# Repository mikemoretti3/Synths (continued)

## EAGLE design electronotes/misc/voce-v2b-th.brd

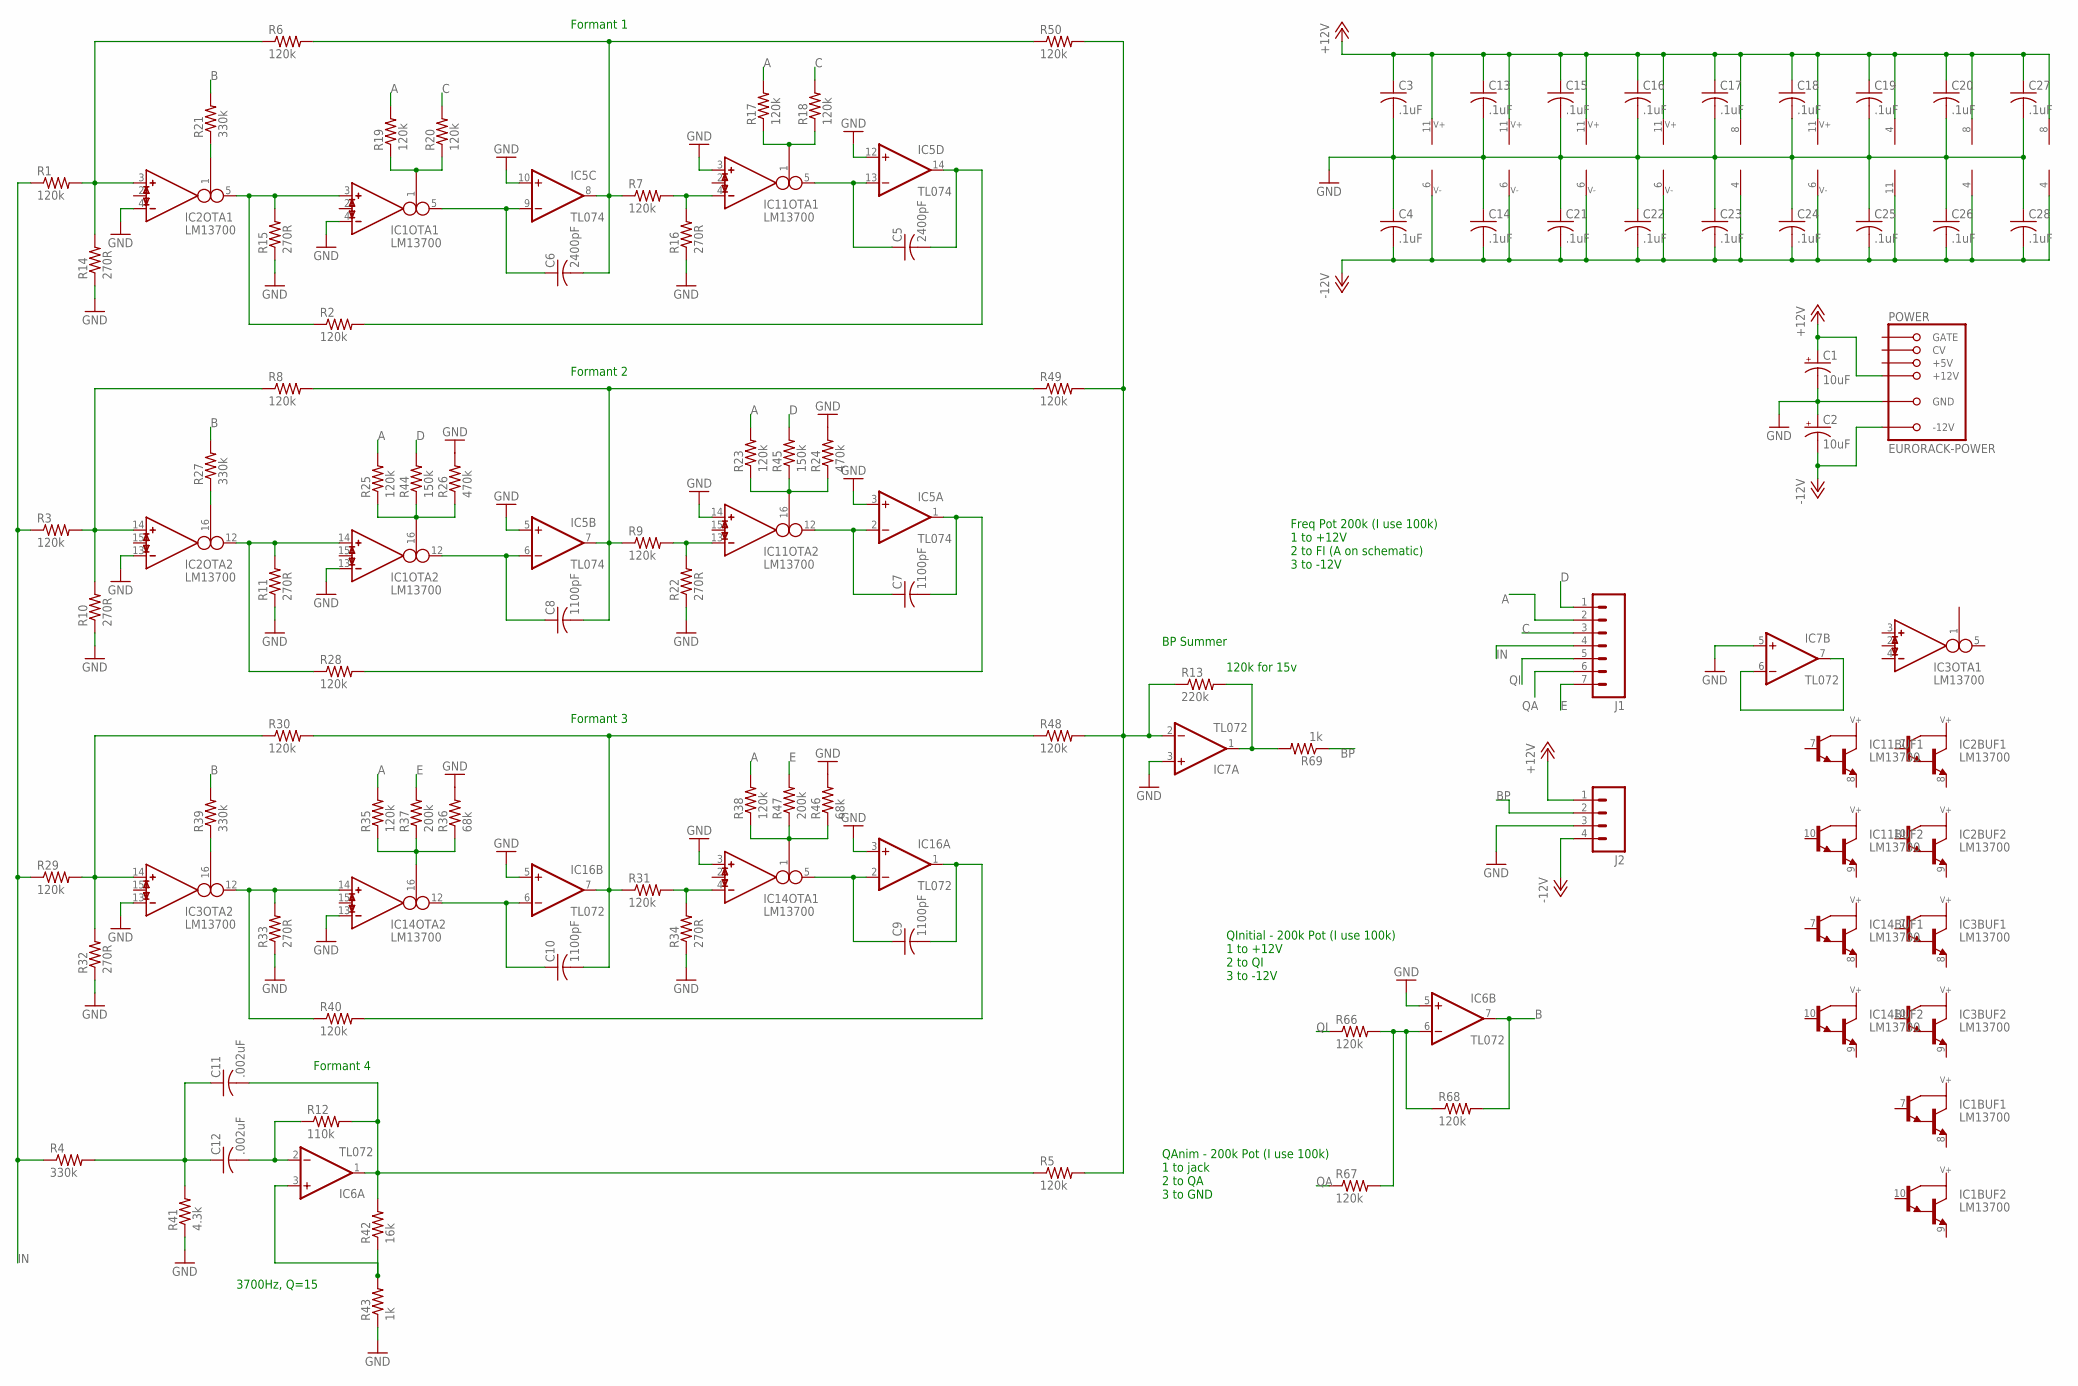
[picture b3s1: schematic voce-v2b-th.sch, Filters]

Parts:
C1, C2: 10uF; E2,5-5
C3, C4, C13, C14, C15, C16, C17, C18, C19, C20, C21, C22, C23, C24, C25, C26, C27, C28: .1uF; C025-025X050
C5, C6: 2400pF; C050-025X075
C7, C8, C9, C10: 1100pF; C050-025X075
C11, C12: .002uF; C050-025X075
IC1, IC2, IC3, IC11, IC14: LM13700; DIL16
IC5: TL074; DIL14
IC6, IC7, IC16: TL072; DIL08
J1: M07LONGPADS; 1X07_LONGPADS
J2: M04LONGPADS; 1X04_LONGPADS
POWER: EURORACK-POWER; PINSHRD_PTH_2X8
R1, R2, R3, R5, R6, R7, R8, R9, R17, R18, R19, R20, R23, R25, R28, R29, R30, R31, R35, R38, R40, R48, R49, R50, R66, R67, R68: 120k; 0204V
R4, R21, R27, R39: 330k; 0204V
R10, R11, R14, R15, R16, R22, R32, R33, R34: 270R; 0204V
R12: 110k; 0204V
R13: 220k; 0204V
R24, R26: 470k; 0204V
R36, R46: 68k; 0204V
R37, R47: 200k; 0204V
R41: 4.3k; 0204V
R42: 16k; 0204V
R43, R69: 1k; 0204V
R44, R45: 150k; 0204V

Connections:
+12V: C1.+, C3.1, C13.1, C15.1, C16.1, C17.1, C18.1, C19.1, C20.1, C27.1, IC1.11 (7), IC2.11 (7), IC3.11 (7), IC5.4 (V+), IC6.8 (V+), IC7.8 (V+), IC11.11 (7), IC14.11 (7), IC16.8 (V+), J2.1, POWER.+12V@1 (+12V), POWER.+12V@2 (+12V)
-12V: C2.-, C4.2, C14.2, C21.2, C22.2, C23.2, C24.2, C25.2, C26.2, C28.2, IC1.6 (4), IC2.6 (4), IC3.6 (4), IC5.11 (V-), IC6.4 (V-), IC7.4 (V-), IC11.6 (4), IC14.6 (4), IC16.4 (V-), J2.4, POWER.-12V@1 (-12V), POWER.-12V@2 (-12V)
A: J1.2, R17.2, R19.2, R23.2, R25.2, R35.2, R38.2
B: IC6.7 (OUT), R21.2, R27.2, R39.2, R68.2
BP: J2.2, R69.1
C: J1.3, R18.2, R20.2
D: J1.1, R44.2, R45.2
E: J1.7, R37.2, R47.2
GND: C1.-, C2.+, C3.2, C4.1, C13.2, C14.1, C15.2, C16.2, C17.2, C18.2, C19.2, C20.2, C21.1, C22.1, C23.1, C24.1, C25.1, C26.1, C27.2, C28.1, IC1.4 (IN_N), IC1.13 (IN_N), IC2.4 (IN_N), IC2.13 (IN_N), IC3.13 (IN_N), IC5.3 (+IN), IC5.5 (+IN), IC5.10 (+IN), IC5.12 (+IN), IC6.5 (+IN), IC7.3 (+IN), IC7.5 (+IN), IC11.3 (IN_P), IC11.14 (IN_P), IC14.3 (IN_P), IC14.13 (IN_N), IC16.3 (+IN), IC16.5 (+IN), J2.3, POWER.GND@1 (GND), POWER.GND@2 (GND), POWER.GND@3 (GND), POWER.GND@4 (GND), POWER.GND@5 (GND), POWER.GND@6 (GND), R10.1, R11.1, R14.1, R15.1, R16.1, R22.1, R24.2, R26.2, R32.1, R33.1, R34.1, R36.2, R41.1, R43.1, R46.2
IN: J1.4, R1.1, R3.1, R4.1, R29.1
unnamed: IC1.3 (IN_P), IC2.5 (OUT), R2.1, R15.2
unnamed: C6.1, IC1.5 (OUT), IC5.9 (-IN)
unnamed: IC2.3 (IN_P), R1.2, R6.1, R14.2
unnamed: IC2.1 (I_BIAS), R21.1
unnamed: IC11.4 (IN_N), R7.2, R16.2
unnamed: C11.2, IC6.1 (OUT), R5.1, R12.2, R42.2
unnamed: C6.2, IC5.8 (OUT), R6.2, R7.1, R50.1
unnamed: IC7.6 (-IN), IC7.7 (OUT)
unnamed: IC1.1 (I_BIAS), R19.1, R20.1
unnamed: C5.1, IC5.13 (-IN), IC11.5 (OUT)
unnamed: C5.2, IC5.14 (OUT), R2.2
unnamed: IC11.1 (I_BIAS), R17.1, R18.1
unnamed: IC1.14 (IN_P), IC2.12 (OUT), R11.2, R28.1
unnamed: C8.1, IC1.12 (OUT), IC5.6 (-IN)
unnamed: IC2.14 (IN_P), R3.2, R8.1, R10.2
unnamed: C8.2, IC5.7 (OUT), R8.2, R9.1, R49.1
unnamed: IC2.16 (I_BIAS), R27.1
unnamed: IC11.13 (IN_N), R9.2, R22.2
unnamed: IC1.16 (I_BIAS), R25.1, R26.1, R44.1
unnamed: IC14.16 (I_BIAS), R35.1, R36.1, R37.1
unnamed: C7.1, IC5.2 (-IN), IC11.12 (OUT)
unnamed: C7.2, IC5.1 (OUT), R28.2
unnamed: IC14.1 (I_BIAS), R38.1, R46.1, R47.1
unnamed: IC3.12 (OUT), IC14.14 (IN_P), R33.2, R40.1
unnamed: C10.1, IC14.12 (OUT), IC16.6 (-IN)
unnamed: IC3.14 (IN_P), R29.2, R30.1, R32.2
unnamed: C10.2, IC16.7 (OUT), R30.2, R31.1, R48.1
unnamed: IC3.16 (I_BIAS), R39.1
unnamed: IC14.4 (IN_N), R31.2, R34.2
unnamed: C9.1, IC14.5 (OUT), IC16.2 (-IN)
unnamed: C9.2, IC16.1 (OUT), R40.2
unnamed: IC7.2 (-IN), R5.2, R13.1, R48.2, R49.2, R50.2
unnamed: IC7.1 (OUT), R13.2, R69.2
unnamed: C12.2, IC6.2 (-IN), R12.1
unnamed: IC6.3 (+IN), R42.1, R43.2
unnamed: C11.1, C12.1, R4.2, R41.2
unnamed: IC6.6 (-IN), R66.2, R67.2, R68.1
unnamed: IC11.16 (I_BIAS), R23.1, R24.1, R45.1
QA: J1.6, R67.1
QI: J1.5, R66.1

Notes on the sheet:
3700Hz, Q=15
Formant 1
Formant 2
Formant 3
BP Summer
QInitial - 200k Pot (I use 100k) 1 to +12V 2 to QI 3 to -12V
QAnim - 200k Pot (I use 100k) 1 to jack 2 to QA 3 to GND
Formant 4
120k for 15v
Freq Pot 200k (I use 100k) 1 to +12V 2 to FI (A on schematic) 3 to -12V

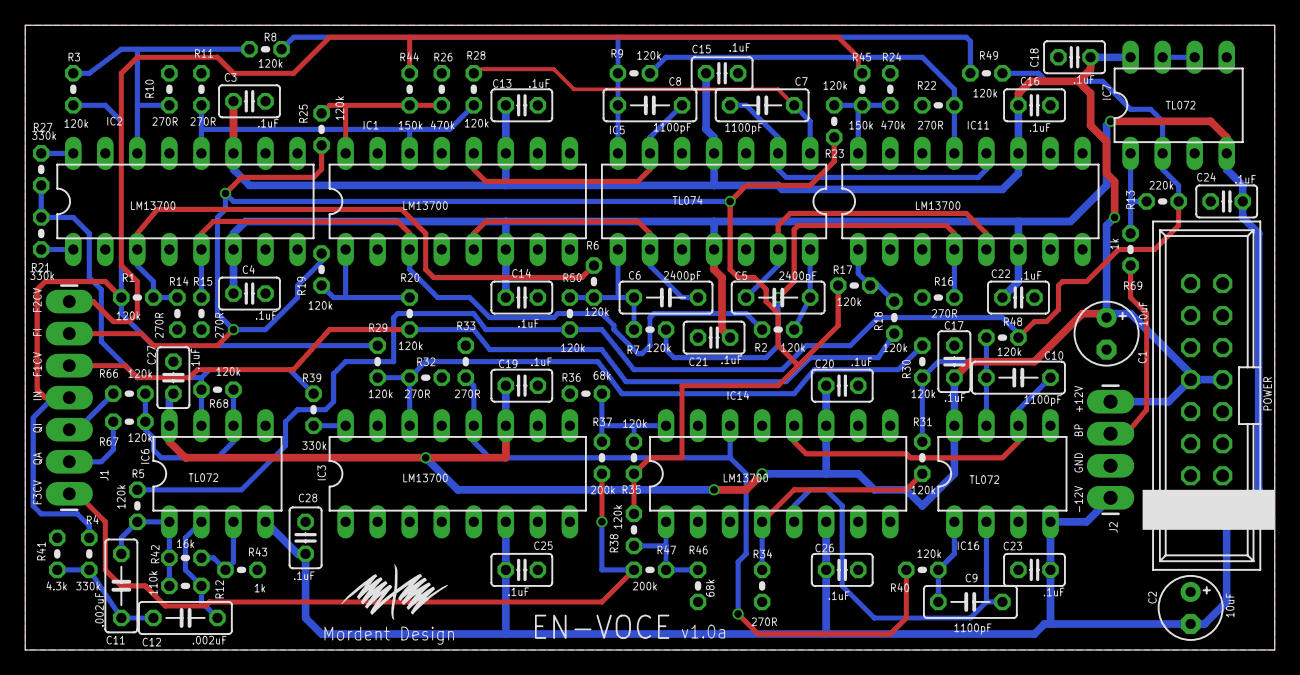
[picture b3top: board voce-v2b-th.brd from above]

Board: 2 copper layers, 99.1 x 49.5 mm, 94 parts (0 on the bottom side), 50 nets.

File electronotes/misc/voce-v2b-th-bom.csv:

"Part";"Value";"Device";"Package";"Description";"";
"C1";"10uF";"CPOL-USE2.5-5";"E2,5-5";"POLARIZED CAPACITOR, American symbol";"";
"C2";"10uF";"CPOL-USE2.5-5";"E2,5-5";"POLARIZED CAPACITOR, American symbol";"";
"C3";".1uF";"C-US025-025X050";"C025-025X050";"CAPACITOR, American symbol";"";
"C4";".1uF";"C-US025-025X050";"C025-025X050";"CAPACITOR, American symbol";"";
"C5";"2400pF";"C-US050-025X075";"C050-025X075";"CAPACITOR, American symbol";"";
"C6";"2400pF";"C-US050-025X075";"C050-025X075";"CAPACITOR, American symbol";"";
"C7";"1100pF";"C-US050-025X075";"C050-025X075";"CAPACITOR, American symbol";"";
"C8";"1100pF";"C-US050-025X075";"C050-025X075";"CAPACITOR, American symbol";"";
"C9";"1100pF";"C-US050-025X075";"C050-025X075";"CAPACITOR, American symbol";"";
"C10";"1100pF";"C-US050-025X075";"C050-025X075";"CAPACITOR, American symbol";"";
"C11";".002uF";"C-US050-025X075";"C050-025X075";"CAPACITOR, American symbol";"";
"C12";".002uF";"C-US050-025X075";"C050-025X075";"CAPACITOR, American symbol";"";
"C13";".1uF";"C-US025-025X050";"C025-025X050";"CAPACITOR, American symbol";"";
"C14";".1uF";"C-US025-025X050";"C025-025X050";"CAPACITOR, American symbol";"";
"C15";".1uF";"C-US025-025X050";"C025-025X050";"CAPACITOR, American symbol";"";
"C16";".1uF";"C-US025-025X050";"C025-025X050";"CAPACITOR, American symbol";"";
"C17";".1uF";"C-US025-025X050";"C025-025X050";"CAPACITOR, American symbol";"";
"C18";".1uF";"C-US025-025X050";"C025-025X050";"CAPACITOR, American symbol";"";
"C19";".1uF";"C-US025-025X050";"C025-025X050";"CAPACITOR, American symbol";"";
"C20";".1uF";"C-US025-025X050";"C025-025X050";"CAPACITOR, American symbol";"";
"C21";".1uF";"C-US025-025X050";"C025-025X050";"CAPACITOR, American symbol";"";
"C22";".1uF";"C-US025-025X050";"C025-025X050";"CAPACITOR, American symbol";"";
"C23";".1uF";"C-US025-025X050";"C025-025X050";"CAPACITOR, American symbol";"";
"C24";".1uF";"C-US025-025X050";"C025-025X050";"CAPACITOR, American symbol";"";
"C25";".1uF";"C-US025-025X050";"C025-025X050";"CAPACITOR, American symbol";"";
"C26";".1uF";"C-US025-025X050";"C025-025X050";"CAPACITOR, American symbol";"";
"C27";".1uF";"C-US025-025X050";"C025-025X050";"CAPACITOR, American symbol";"";
"C28";".1uF";"C-US025-025X050";"C025-025X050";"CAPACITOR, American symbol";"";
"IC1";"LM13700";"LM13700N";"DIL16";"Dual OTA with buffers";"";
"IC2";"LM13700";"LM13700N";"DIL16";"Dual OTA with buffers";"";
"IC3";"LM13700";"LM13700N";"DIL16";"Dual OTA with buffers";"";
"IC5";"TL074";"TL074P";"DIL14";"OP AMP";"";
"IC6";"TL072";"TL072P";"DIL08";"OP AMP";"";
"IC7";"TL072";"TL072P";"DIL08";"OP AMP";"";
"IC11";"LM13700";"LM13700N";"DIL16";"Dual OTA with buffers";"";
"IC14";"LM13700";"LM13700N";"DIL16";"Dual OTA with buffers";"";
"IC16";"TL072";"TL072P";"DIL08";"OP AMP";"";
"J1";"";"M07LONGPADS";"1X07_LONGPADS";"Header 7";"";
"J2";"";"M04LONGPADS";"1X04_LONGPADS";"Header 4";"";
"POWER";"EURORACK-POWER";"EURORACK-POWER";"PINSHRD_PTH_2X8";"";"";
"R1";"120k";"R-US_0204/2V";"0204V";"RESISTOR, American symbol";"";
"R2";"120k";"R-US_0204/2V";"0204V";"RESISTOR, American symbol";"";
"R3";"120k";"R-US_0204/2V";"0204V";"RESISTOR, American symbol";"";
"R4";"330k";"R-US_0204/2V";"0204V";"RESISTOR, American symbol";"";
"R5";"120k";"R-US_0204/2V";"0204V";"RESISTOR, American symbol";"";
"R6";"120k";"R-US_0204/2V";"0204V";"RESISTOR, American symbol";"";
"R7";"120k";"R-US_0204/2V";"0204V";"RESISTOR, American symbol";"";
"R8";"120k";"R-US_0204/2V";"0204V";"RESISTOR, American symbol";"";
"R9";"120k";"R-US_0204/2V";"0204V";"RESISTOR, American symbol";"";
"R10";"270R";"R-US_0204/2V";"0204V";"RESISTOR, American symbol";"";
"R11";"270R";"R-US_0204/2V";"0204V";"RESISTOR, American symbol";"";
"R12";"110k";"R-US_0204/2V";"0204V";"RESISTOR, American symbol";"";
"R13";"220k";"R-US_0204/2V";"0204V";"RESISTOR, American symbol";"";
"R14";"270R";"R-US_0204/2V";"0204V";"RESISTOR, American symbol";"";
"R15";"270R";"R-US_0204/2V";"0204V";"RESISTOR, American symbol";"";
"R16";"270R";"R-US_0204/2V";"0204V";"RESISTOR, American symbol";"";
"R17";"120k";"R-US_0204/2V";"0204V";"RESISTOR, American symbol";"";
"R18";"120k";"R-US_0204/2V";"0204V";"RESISTOR, American symbol";"";
"R19";"120k";"R-US_0204/2V";"0204V";"RESISTOR, American symbol";"";
"R20";"120k";"R-US_0204/2V";"0204V";"RESISTOR, American symbol";"";
"R21";"330k";"R-US_0204/2V";"0204V";"RESISTOR, American symbol";"";
"R22";"270R";"R-US_0204/2V";"0204V";"RESISTOR, American symbol";"";
"R23";"120k";"R-US_0204/2V";"0204V";"RESISTOR, American symbol";"";
"R24";"470k";"R-US_0204/2V";"0204V";"RESISTOR, American symbol";"";
"R25";"120k";"R-US_0204/2V";"0204V";"RESISTOR, American symbol";"";
"R26";"470k";"R-US_0204/2V";"0204V";"RESISTOR, American symbol";"";
"R27";"330k";"R-US_0204/2V";"0204V";"RESISTOR, American symbol";"";
"R28";"120k";"R-US_0204/2V";"0204V";"RESISTOR, American symbol";"";
"R29";"120k";"R-US_0204/2V";"0204V";"RESISTOR, American symbol";"";
"R30";"120k";"R-US_0204/2V";"0204V";"RESISTOR, American symbol";"";
"R31";"120k";"R-US_0204/2V";"0204V";"RESISTOR, American symbol";"";
"R32";"270R";"R-US_0204/2V";"0204V";"RESISTOR, American symbol";"";
"R33";"270R";"R-US_0204/2V";"0204V";"RESISTOR, American symbol";"";
"R34";"270R";"R-US_0204/2V";"0204V";"RESISTOR, American symbol";"";
"R35";"120k";"R-US_0204/2V";"0204V";"RESISTOR, American symbol";"";
"R36";"68k";"R-US_0204/2V";"0204V";"RESISTOR, American symbol";"";
"R37";"200k";"R-US_0204/2V";"0204V";"RESISTOR, American symbol";"";
"R38";"120k";"R-US_0204/2V";"0204V";"RESISTOR, American symbol";"";
"R39";"330k";"R-US_0204/2V";"0204V";"RESISTOR, American symbol";"";
"R40";"120k";"R-US_0204/2V";"0204V";"RESISTOR, American symbol";"";
"R41";"4.3k";"R-US_0204/2V";"0204V";"RESISTOR, American symbol";"";
"R42";"16k";"R-US_0204/2V";"0204V";"RESISTOR, American symbol";"";
"R43";"1k";"R-US_0204/2V";"0204V";"RESISTOR, American symbol";"";
"R44";"150k";"R-US_0204/2V";"0204V";"RESISTOR, American symbol";"";
"R45";"150k";"R-US_0204/2V";"0204V";"RESISTOR, American symbol";"";
"R46";"68k";"R-US_0204/2V";"0204V";"RESISTOR, American symbol";"";
"R47";"200k";"R-US_0204/2V";"0204V";"RESISTOR, American symbol";"";
"R48";"120k";"R-US_0204/2V";"0204V";"RESISTOR, American symbol";"";
"R49";"120k";"R-US_0204/2V";"0204V";"RESISTOR, American symbol";"";
"R50";"120k";"R-US_0204/2V";"0204V";"RESISTOR, American symbol";"";
"R66";"120k";"R-US_0204/2V";"0204V";"RESISTOR, American symbol";"";
"R67";"120k";"R-US_0204/2V";"0204V";"RESISTOR, American symbol";"";
"R68";"120k";"R-US_0204/2V";"0204V";"RESISTOR, American symbol";"";
"R69";"1k";"R-US_0204/2V";"0204V";"RESISTOR, American symbol";"";

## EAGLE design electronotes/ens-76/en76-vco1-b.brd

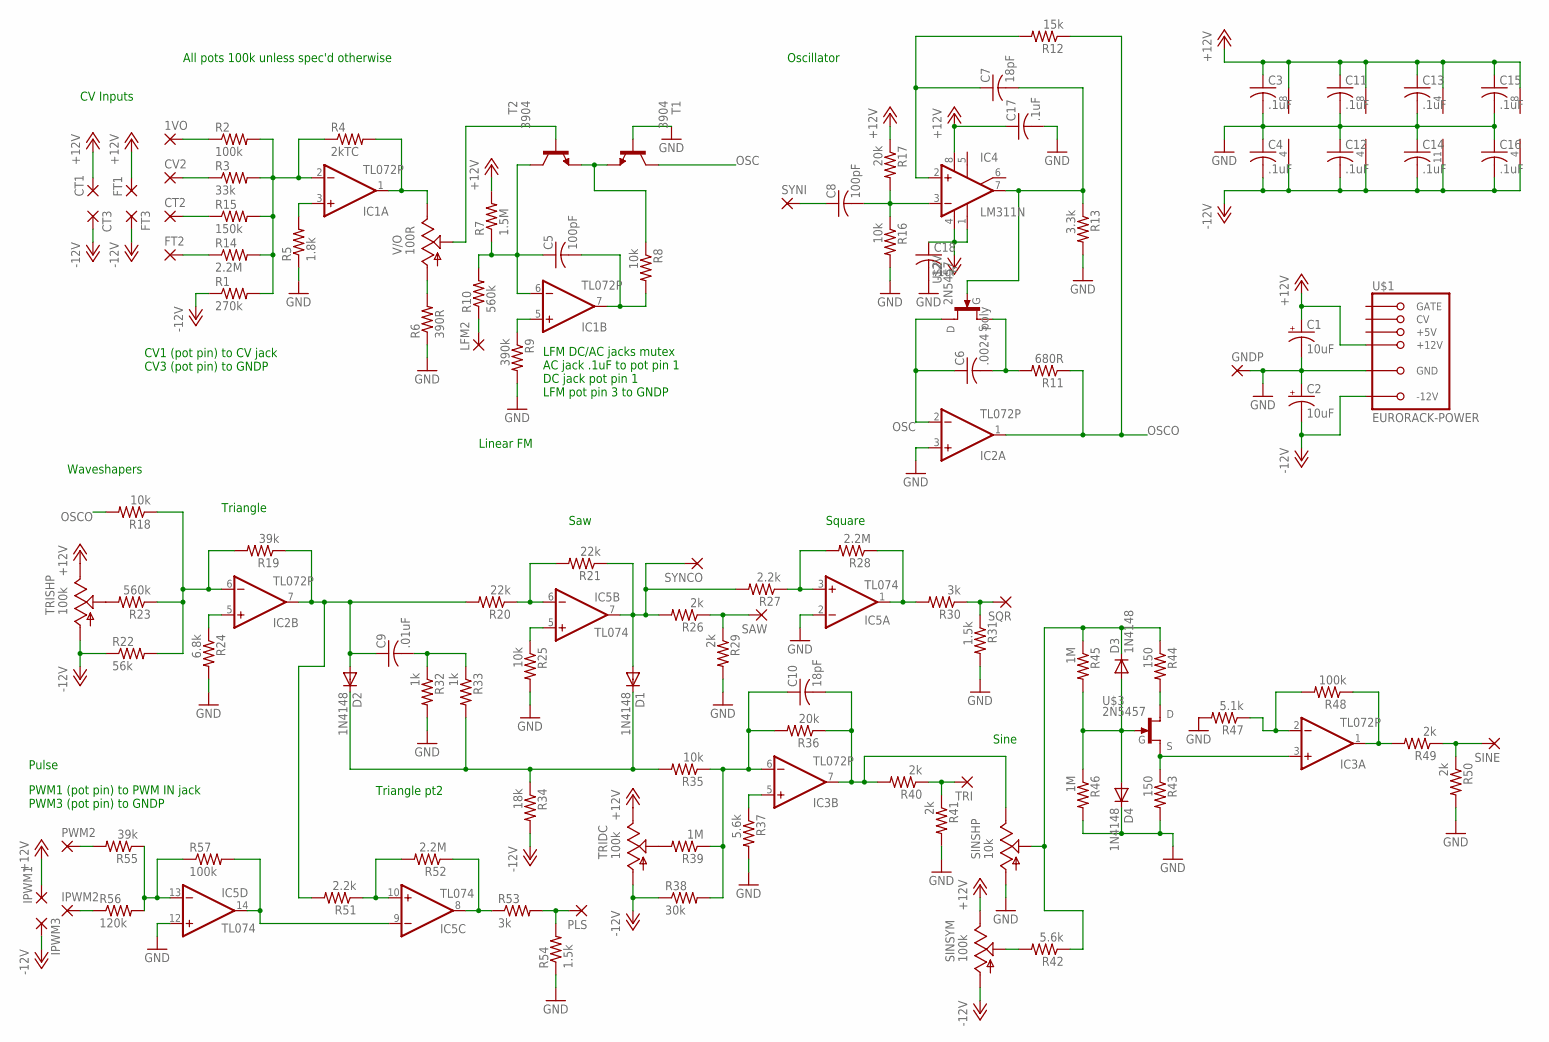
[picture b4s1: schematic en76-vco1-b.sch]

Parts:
1VO: 2,54/1,0
C1, C2: 10uF; E2-5
C3, C4, C11, C12, C13, C14, C15, C16, C17, C18: .1uF; C050-025X075
C5, C8: 100pF; C050-025X075
C6: .0024 poly; C050-025X075
C7, C10: 18pF; C050-025X075
C9: .01uF; C050-025X075
CT1, CT2, CT3: 2,54/1,0
CV2: 2,54/1,0
D1, D2, D3, D4: 1N4148; DO35-7
FT1, FT2, FT3: 2,54/1,0
GNDP: 2,54/1,0
IC1, IC2, IC3: TL072P; DIL08
IC4: LM311N; DIL08
IC5: TL074; DIL14
IPWM1, IPWM2, IPWM3: 2,54/1,0
LFM2: 2,54/1,0
PLS: 2,54/1,0
PWM2: 2,54/1,0
R1: 270k; 0207/10
R2, R48, R57: 100k; 0207/10
R3: 33k; 0207/10
R4: 2kTC; 0207/10
R5: 1.8k; 0207/10
R6: 390R; 0207/10
R7: 1.5M; 0207/10
R8, R16, R18, R25, R35: 10k; 0207/10
R9: 390k; 0207/10
R10, R23: 560k; 0207/10
R11: 680R; 0207/10
R12: 15k; 0207/10
R13: 3.3k; 0207/10
R14, R28, R52: 2.2M; 0207/10
R15: 150k; 0207/10
R17, R36: 20k; 0207/10
R19, R55: 39k; 0207/10
R20, R21: 22k; 0207/10
R22: 56k; 0207/10
R24: 6.8k; 0207/10
R26, R29, R40, R41, R49, R50: 2k; 0207/10
R27, R51: 2.2k; 0207/10
R30, R53: 3k; 0207/10
R31, R54: 1.5k; 0207/10
R32, R33: 1k; 0207/10
R34: 18k; 0207/10
R37, R42: 5.6k; 0207/10
R38: 30k; 0207/10
R39, R45, R46: 1M; 0207/10
R43, R44: 150; 0207/10
R47: 5.1k; 0207/10
R56: 120k; 0207/10
SAW: 2,54/1,0
SINE: 2,54/1,0
SINSHP: 10k; RJ9W
SINSYM: 100k; RJ9W
SQR: 2,54/1,0
SYNCO: 2,54/1,0
SYNI: 2,54/1,0
T1, T2: 3904; TO92-EBC
TRI: 2,54/1,0
TRIDC: 100k; RJ9W
TRISHP: 100k; RJ9W
U$1: EURORACK-POWER; PINSHRD_PTH_2X8
U$2, U$3: 2N5457; TO-92
V/O: 100R; RJ9W

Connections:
+12V: C1.+, C3.1, C11.1, C13.1, C15.1, C17.1, CT1.1, FT1.1, IC1.8 (V+), IC2.8 (V+), IC3.8 (V+), IC4.8 (V+), IC5.4 (V+), IPWM1.1, R7.2, R17.1, SINSYM.E, TRIDC.E, TRISHP.E, U$1.+12V@1 (+12V), U$1.+12V@2 (+12V)
-12V: C2.-, C4.2, C12.2, C14.2, C16.2, C18.1, CT3.1, FT3.1, IC1.4 (V-), IC2.4 (V-), IC3.4 (V-), IC4.1 (GND), IC4.4 (V-), IC5.11 (V-), IPWM3.1, R1.1, R22.1, R34.2, R38.1, SINSYM.A, TRIDC.A, TRISHP.A, U$1.-12V@1 (-12V), U$1.-12V@2 (-12V)
GND: C1.-, C2.+, C3.2, C4.1, C11.2, C12.1, C13.2, C14.1, C15.2, C16.1, C17.2, C18.2, D4.C, GNDP.1, IC2.3 (+IN), IC5.2 (-IN), IC5.12 (+IN), R5.1, R6.1, R9.2, R13.2, R16.2, R24.2, R25.2, R29.2, R31.2, R32.2, R37.2, R41.2, R43.2, R46.2, R47.2, R50.2, R54.1, SINSHP.A, T1.B, U$1.GND@1 (GND), U$1.GND@2 (GND), U$1.GND@3 (GND), U$1.GND@4 (GND), U$1.GND@5 (GND), U$1.GND@6 (GND)
unnamed: CT2.1, R15.1
unnamed: CV2.1, R3.1
unnamed: 1VO.1, R2.1
unnamed: T2.B, V/O.S
unnamed: IC1.3 (+IN), R5.2
unnamed: IC1.2 (-IN), R1.2, R2.2, R3.2, R4.1, R14.2, R15.2
unnamed: IC1.1 (OUT), R4.2, V/O.E
unnamed: R6.2, V/O.A
unnamed: C5.1, IC1.6 (-IN), R7.1, R10.2, T2.C
unnamed: R8.1, T1.E, T2.E
unnamed: C5.2, IC1.7 (OUT), R8.2
unnamed: FT2.1, R14.1
unnamed: LFM2.1, R10.1
unnamed: IC1.5 (+IN), R9.1
unnamed: C7.1, IC4.2 (+IN), R12.2
unnamed: C7.2, IC4.7 (OUT), R13.1, U$2.3 (G)
unnamed: R23.2, TRISHP.S
unnamed: C6.2, R11.2, U$2.2 (S)
unnamed: D1.A, IC5.7 (OUT), R21.1, R26.2, R27.2, SYNCO.1
unnamed: C8.1, SYNI.1
unnamed: C8.2, IC4.3 (-IN), R16.1, R17.2
unnamed: PWM2.1, R55.2
unnamed: IC2.5 (+IN), R24.1
unnamed: IC2.6 (-IN), R18.1, R19.2, R22.2, R23.1
unnamed: R26.1, R29.1, SAW.1
unnamed: IC5.6 (-IN), R20.1, R21.2
unnamed: C9.2, R32.1, R33.1
unnamed: IC5.5 (+IN), R25.1
unnamed: IC5.3 (+IN), R27.1, R28.2
unnamed: IC5.1 (OUT), R28.1, R30.2
unnamed: R30.1, R31.1, SQR.1
unnamed: D1.C, D2.C, R33.2, R34.1, R35.2
unnamed: R40.1, R41.1, TRI.1
unnamed: C10.2, IC3.7 (OUT), R36.1, R40.2, SINSHP.E
unnamed: IC3.5 (+IN), R37.1
unnamed: R39.2, TRIDC.S
unnamed: C10.1, IC3.6 (-IN), R35.1, R36.2, R38.2, R39.1
unnamed: IC3.3 (+IN), R43.1, U$3.2 (S)
unnamed: R44.2, U$3.1 (D)
unnamed: D3.A, D4.A, R45.2, R46.1, U$3.3 (G)
unnamed: R42.2, SINSYM.S
unnamed: D3.C, R42.1, R44.1, R45.1, SINSHP.S
unnamed: IC3.2 (-IN), R47.1, R48.2
unnamed: R49.1, R50.1, SINE.1
unnamed: IC3.1 (OUT), R48.1, R49.2
unnamed: IC5.9 (-IN), IC5.14 (OUT), R57.2
unnamed: IC5.10 (+IN), R51.1, R52.2
unnamed: IC5.8 (OUT), R52.1, R53.1
unnamed: PLS.1, R53.2, R54.2
unnamed: C9.1, D2.A, IC2.7 (OUT), R19.1, R20.2, R51.2
unnamed: IPWM2.1, R56.1
unnamed: IC5.13 (-IN), R55.1, R56.2, R57.1
OSC: C6.1, IC2.2 (-IN), T1.C, U$2.1 (D)
OSCO: IC2.1 (OUT), R11.1, R12.1, R18.2

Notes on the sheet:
CV1 (pot pin) to CV jack CV3 (pot pin) to GNDP
LFM DC/AC jacks mutex AC jack .1uF to pot pin 1 DC jack pot pin 1 LFM pot pin 3 to GNDP
All pots 100k unless spec'd otherwise
PWM1 (pot pin) to PWM IN jack PWM3 (pot pin) to GNDP
CV Inputs
Oscillator
Waveshapers
Triangle
Saw
Square
Triangle pt2
Sine
Pulse
Linear FM

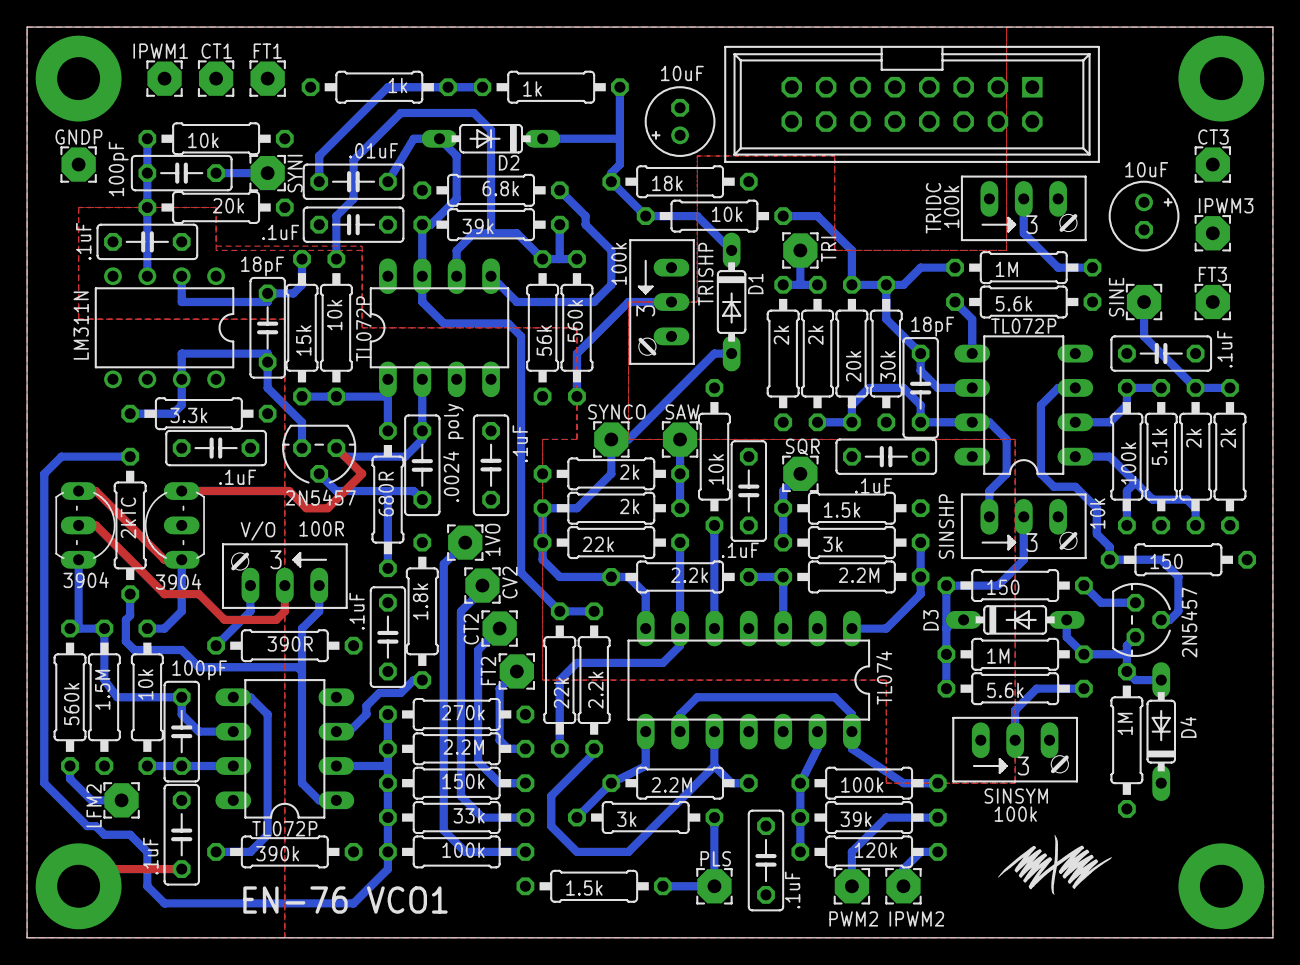
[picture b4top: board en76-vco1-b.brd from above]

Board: 2 copper layers, 92.1 x 67.3 mm, 115 parts (0 on the bottom side), 57 nets.

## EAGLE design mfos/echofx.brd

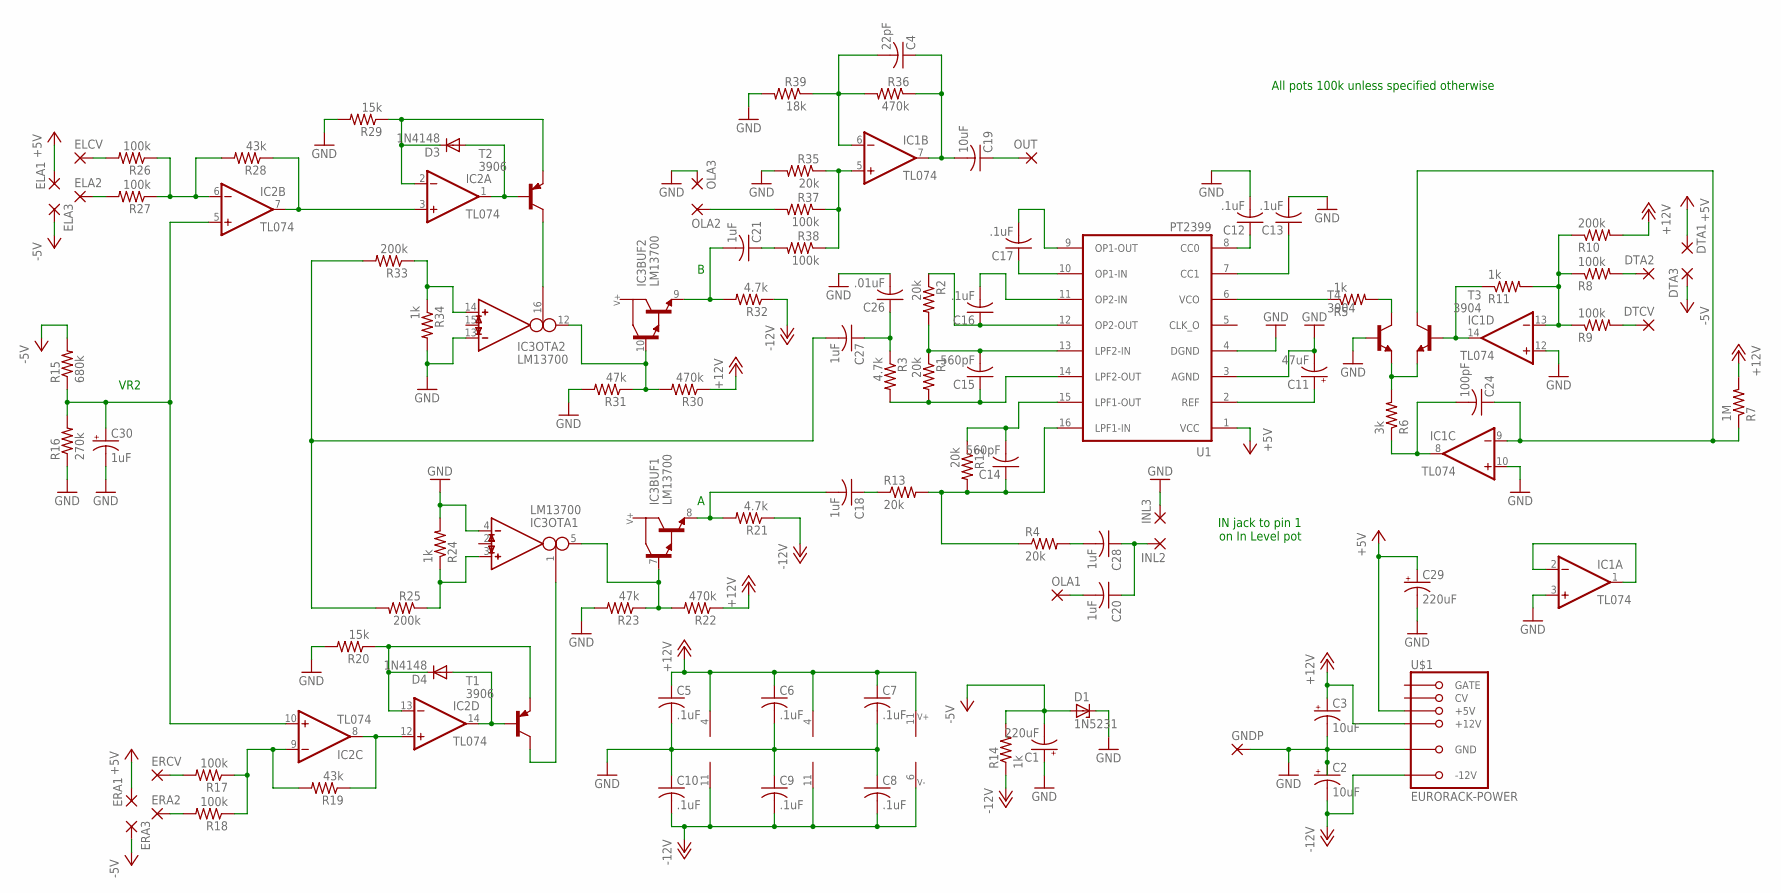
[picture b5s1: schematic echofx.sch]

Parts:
C1, C29: 220uF; E2-5
C2, C3: 10uF; E2-5
C4: 22pF; C050-025X075
C5, C6, C7, C8, C9, C10, C12, C13, C16, C17: .1uF; C050-025X075
C11: 47uF; E2-5
C14, C15: 560pF; C050-025X075
C18, C20, C21, C27, C28: 1uF; C050-025X075
C19: 10uF; C050-025X075
C24: 100pF; C050-025X075
C26: .01uF; C050-025X075
C30: 1uF; E2-5
D1: 1N5231; DO34Z7
D3, D4: 1N4148; DO35-7
DTA1, DTA2, DTA3: 2,54/1,0
DTCV: 2,54/1,0
ELA1, ELA2, ELA3: 2,54/1,0
ELCV: 2,54/1,0
ERA1, ERA2, ERA3: 2,54/1,0
ERCV: 2,54/1,0
GNDP: 2,54/1,0
IC1, IC2: TL074; DIL14
IC3: LM13700; DIL16
INL2, INL3: 2,54/1,0
OLA1, OLA2, OLA3: 2,54/1,0
OUT: 2,54/1,0
R1, R2, R4, R12, R13, R35: 20k; 0207/10
R3, R21, R32: 4.7k; 0207/10
R5, R11, R14, R24, R34: 1k; 0207/10
R6: 3k; 0207/10
R7: 1M; 0207/10
R8, R9, R17, R18, R26, R27, R37, R38: 100k; 0207/10
R10, R25, R33: 200k; 0207/10
R15: 680k; 0207/10
R16: 270k; 0207/10
R19, R28: 43k; 0207/10
R20, R29: 15k; 0207/10
R22, R30, R36: 470k; 0207/10
R23, R31: 47k; 0207/10
R39: 18k; 0207/10
T1, T2: 3906; TO92-EBC
T3, T4: 3904; TO92-EBC
U1: PT2399; DIL16
U$1: EURORACK-POWER; PINSHRD_PTH_2X8

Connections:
+5V: C29.+, DTA1.1, ELA1.1, ERA1.1, U1.1 (VCC), U$1.+5V@1 (+5V), U$1.+5V@2 (+5V)
+12V: C3.+, C5.1, C6.1, C7.1, IC1.4 (V+), IC2.4 (V+), IC3.11 (7), R7.2, R10.2, R22.1, R30.1, U$1.+12V@1 (+12V), U$1.+12V@2 (+12V)
-5V: C1.-, D1.A, DTA3.1, ELA3.1, ERA3.1, R14.2, R15.2
-12V: C2.-, C8.2, C9.2, C10.2, IC1.11 (V-), IC2.11 (V-), IC3.6 (4), R14.1, R21.1, R32.1, U$1.-12V@1 (-12V), U$1.-12V@2 (-12V)
GND: C1.+, C2.+, C3.-, C5.2, C6.2, C7.2, C8.1, C9.1, C10.1, C11.-, C12.2, C13.2, C26.2, C29.-, C30.-, D1.C, GNDP.1, IC1.3 (+IN), IC1.10 (+IN), IC1.12 (+IN), IC3.4 (IN_N), IC3.13 (IN_N), INL3.1, OLA3.1, R16.1, R20.2, R23.2, R24.2, R29.2, R31.2, R34.2, R35.2, R39.2, T4.B, U1.3 (AGND), U1.4 (DGND), U$1.GND@1 (GND), U$1.GND@2 (GND), U$1.GND@3 (GND), U$1.GND@4 (GND), U$1.GND@5 (GND), U$1.GND@6 (GND)
unnamed: C11.+, U1.2 (REF)
unnamed: IC1.14 (OUT), R11.1, T3.B
unnamed: C12.1, U1.8 (CC0)
unnamed: C13.1, U1.7 (CC1)
unnamed: C17.1, U1.10 (OP1-IN)
unnamed: C17.2, U1.9 (OP1-OUT)
unnamed: C16.2, U1.11 (OP2-IN)
unnamed: C16.1, R2.1, U1.12 (OP2-OUT)
unnamed: C15.2, R1.1, R2.2, U1.13 (LPF2-IN)
unnamed: C15.1, R1.2, R3.2, U1.14 (LPF2-OUT)
unnamed: C26.1, C27.1, R3.1
unnamed: C20.1, C28.1, INL2.1
unnamed: C28.2, R4.2
unnamed: R5.1, U1.6 (VCO)
unnamed: C24.1, IC1.9 (-IN), R7.1, T3.C
unnamed: C24.2, IC1.8 (OUT), R6.1
unnamed: R6.2, T3.E, T4.E
unnamed: R5.2, T4.C
unnamed: DTA2.1, R8.2
unnamed: DTCV.1, R9.2
unnamed: IC1.13 (-IN), R8.1, R9.1, R10.1, R11.2
unnamed: C14.2, R12.1, U1.15 (LPF1-OUT)
unnamed: C14.1, R4.1, R12.2, R13.2, U1.16 (LPF1-IN)
unnamed: C18.1, R13.1
unnamed: ERCV.1, R17.2
unnamed: C27.2, R25.2, R33.2
unnamed: ERA2.1, R18.2
unnamed: IC2.9 (-IN), R17.1, R18.1, R19.2
unnamed: IC2.8 (OUT), IC2.12 (+IN), R19.1
unnamed: D4.C, IC2.13 (-IN), R20.1, T1.E
unnamed: D4.A, IC2.14 (OUT), T1.B
unnamed: C18.2, IC3.8 (E), R21.2
unnamed: IC3.1 (I_BIAS), T1.C
unnamed: IC3.5 (OUT), IC3.7 (B), R22.2, R23.1
unnamed: IC3.3 (IN_P), R24.1, R25.1
unnamed: ELCV.1, R26.2
unnamed: ELA2.1, R27.2
unnamed: IC2.6 (-IN), R26.1, R27.1, R28.2
unnamed: IC2.3 (+IN), IC2.7 (OUT), R28.1
unnamed: D3.C, IC2.2 (-IN), R29.1, T2.E
unnamed: D3.A, IC2.1 (OUT), T2.B
unnamed: IC3.16 (I_BIAS), T2.C
unnamed: IC3.10 (B), IC3.12 (OUT), R30.2, R31.1
unnamed: C21.2, IC3.9 (E), R32.2
unnamed: IC3.14 (IN_P), R33.1, R34.1
unnamed: IC1.5 (+IN), R35.1, R37.1, R38.1
unnamed: C30.+, IC2.5 (+IN), IC2.10 (+IN), R15.1, R16.2
unnamed: C4.2, IC1.6 (-IN), R36.2, R39.1
unnamed: C4.1, C19.2, IC1.7 (OUT), R36.1
unnamed: C19.1, OUT.1
unnamed: OLA2.1, R37.2
unnamed: C20.2, OLA1.1
unnamed: C21.1, R38.2
unnamed: IC1.1 (OUT), IC1.2 (-IN)

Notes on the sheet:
All pots 100k unless specified otherwise
IN jack to pin 1 on In Level pot
VR2

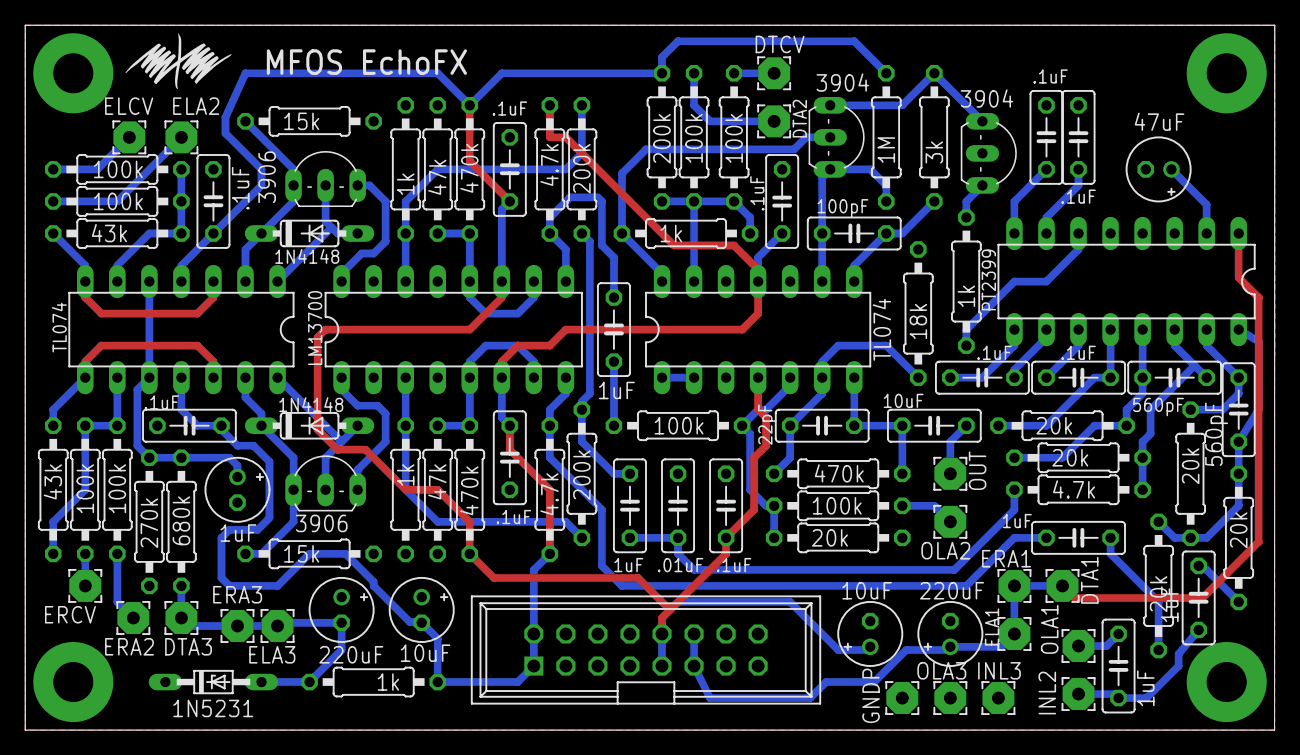
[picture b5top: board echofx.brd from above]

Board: 2 copper layers, 99.1 x 55.9 mm, 97 parts (0 on the bottom side), 59 nets.
